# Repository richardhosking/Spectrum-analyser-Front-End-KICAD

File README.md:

# Spectrum-analyser-Front-End-KICAD

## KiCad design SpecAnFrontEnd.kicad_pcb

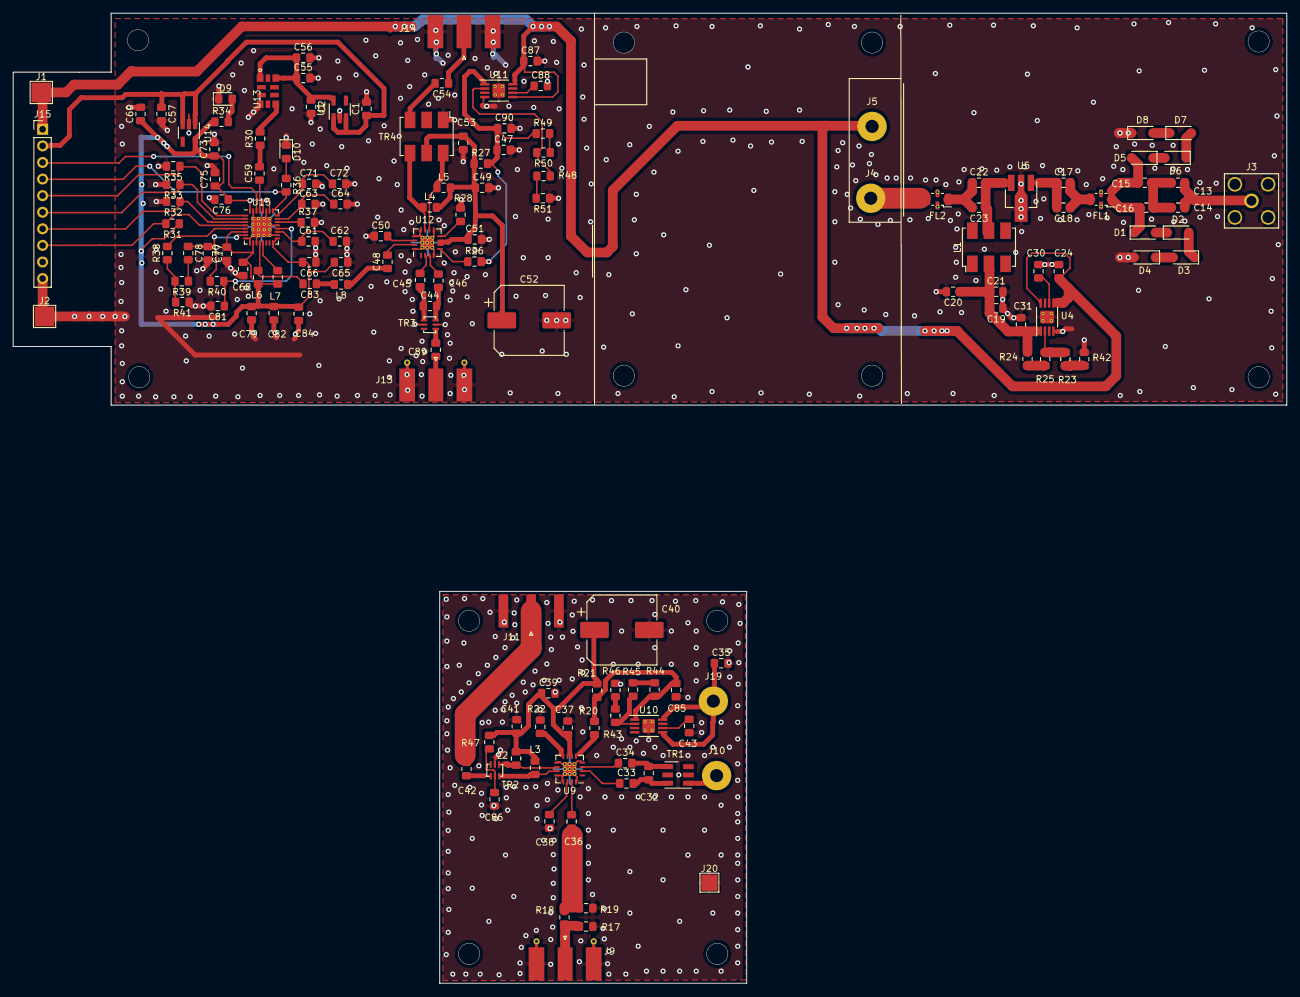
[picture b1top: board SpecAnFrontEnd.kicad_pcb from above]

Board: 2 copper layers, 195.0 x 148.5 mm, 151 parts (0 on the bottom side), 90 nets.

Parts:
C1, C2, C19, C39, C51, C57, C60: 1u; C_0805_2012Metric_Pad1.15x1.40mm_HandSolder
C13, C16, C18, C23, C33, C34, C36, C38, C55, C62, C64, C65, C72, C73, C75, C84: 100n; C_0805_2012Metric_Pad1.15x1.40mm_HandSolder
C14, C15, C17, C21, C22, C45, C46, C48, C50, C56, C79, C82: 100p; C_0805_2012Metric_Pad1.15x1.40mm_HandSolder
C20, C30, C37, C41, C43, C47, C49, C53, C86, C88: 10n; C_0805_2012Metric_Pad1.15x1.40mm_HandSolder
C24, C31, C35, C85, C87, C90: 10u; C_0805_2012Metric_Pad1.15x1.40mm_HandSolder
C32, C44: 0.6p; C_0805_2012Metric_Pad1.15x1.40mm_HandSolder
C40, C52: 220u; CP_Elec_10x10.5
C42, C89: 4p7; C_0805_2012Metric_Pad1.15x1.40mm_HandSolder
C54, C59, C83: 1n; C_0805_2012Metric_Pad1.15x1.40mm_HandSolder
C61, C63, C66, C68, C70, C71, C76: 10p; C_0805_2012Metric_Pad1.15x1.40mm_HandSolder
C77: 2n7; C_0805_2012Metric_Pad1.15x1.40mm_HandSolder
C78: 47n; C_0805_2012Metric_Pad1.15x1.40mm_HandSolder
C81: 680p; C_0805_2012Metric_Pad1.15x1.40mm_HandSolder
D1, D2, D3, D4, D5, D6, D7, D8: MMSD301T1G; D_SOD-123
D9: Power; D_0805_2012Metric_Pad1.15x1.40mm_HandSolder
D10: LOCK; D_0805_2012Metric_Pad1.15x1.40mm_HandSolder
FL1, FL2: LFCN-2600; Filter_Mini-Circuits_FV1206
J1: +V; TestPoint_Pad_3.0x3.0mm
J2: TestPoint_Pad_3.0x3.0mm
J3: Input; SMA_Amphenol_132203-12_Horizontal
J4: OUT to First Mixer; SolderWirePad_1x01_Drill2mm
J5, J19: +V; SolderWirePad_1x01_Drill2mm
J9: LO IN; SMA_Molex_73251-1153_EdgeMount_Horizontal
J10: Conn_Coaxial; SolderWirePad_1x01_Drill2mm
J11: Conn_Coaxial; SMA_Amphenol_132289_EdgeMount
J13, J14: Conn_Coaxial; SMA_Molex_73251-1153_EdgeMount_Horizontal
J15: Data; PinHeader_1x10_P2.54mm_Vertical
J20: GND; TestPoint_Pad_2.5x2.5mm
L1: ADCH-80+; Mini-Circuits_CD542_H2.84mm
L2, L3: 2nH; L_0805_2012Metric_Pad1.15x1.40mm_HandSolder
L4, L5: 22n; L_0805_2012Metric_Pad1.15x1.40mm_HandSolder
L6, L7: 7n5; L_0805_2012Metric_Pad1.15x1.40mm_HandSolder
L8: 1n9; L_0805_2012Metric_Pad1.15x1.40mm_HandSolder
R17, R19, R38: DNI; R_0805_2012Metric_Pad1.15x1.40mm_HandSolder
R18, R30, R41, R47: 0R; R_0805_2012Metric_Pad1.15x1.40mm_HandSolder
R20, R26, R31, R32, R33, R35: 10K; R_0805_2012Metric_Pad1.15x1.40mm_HandSolder
R21, R27: 0.5R; R_0805_2012Metric_Pad1.15x1.40mm_HandSolder
R22, R28: 4K75; R_0805_2012Metric_Pad1.15x1.40mm_HandSolder
R23, R43, R48: 22K; R_0805_2012Metric_Pad1.15x1.40mm_HandSolder
R24, R44, R49: 68K; R_0805_2012Metric_Pad1.15x1.40mm_HandSolder
R25, R45, R50: 8K2; R_0805_2012Metric_Pad1.15x1.40mm_HandSolder
R34, R36: 100R; R_0805_2012Metric_Pad1.15x1.40mm_HandSolder
R37: 4K7; R_0805_2012Metric_Pad1.15x1.40mm_HandSolder
R39: 360R; R_0805_2012Metric_Pad1.15x1.40mm_HandSolder
R40: 1K; R_0805_2012Metric_Pad1.15x1.40mm_HandSolder
R42, R46, R51: 1K8; R_0805_2012Metric_Pad1.15x1.40mm_HandSolder
TR1: TCM1-63AX; Mini-Circuits_DB1627
TR2, TR3: NCS1-422; Minicircuits_GE0805C-1
TR4: ADT4-5WT; Mini-Circuits_CD637_H5.23mm
U1, U14: ADP150; SOT-23-5_HandSoldering
U4, U10, U11: TPSA49; MSOP-8-1EP_3x3mm_P0.65mm_EP1.95x2.15mm_ThermalVias
U5: MMG38151; SOT-89-3_Handsoldering
U9, U12: LTC5510; QFN-16-1EP_4x4mm_P0.65mm_EP2.1x2.1mm_ThermalVias
U13: SiT5156
U15: ADF4351; LFCSP-32-1EP_5x5mm_P0.5mm_EP3.1x3.1mm_ThermalVias

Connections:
+V: C1.1, C24.1, C35.1, C57.1, C87.1, J1.1, J5.1, J15.1, J19.1, U1.1, U1.3, U4.5, U4.8, U10.5, U10.8, U11.5, U11.8, U14.1, U14.3
/First Mixer/U9VCC: C37.1, C39.1, C40.1, C41.1, L2.2, L3.1, R21.1, R47.1, U9.6, U9.7
/Second LO/AVDD2LO: C60.1, C65.2, C66.2, C68.2, C70.2, C73.1, C75.1, C76.1, C79.1, C82.1, C84.1, L6.2, L7.1, R31.1, R34.1, U14.5, U15.6, U15.10, U15.16, U15.17, U15.26, U15.28, U15.32
/Second LO/AVDDOSC: C2.1, C55.1, C56.1, U1.5, U13.1, U13.9
GND: C1.2, C2.2, C19.1, C20.2, C21.2, C24.2, C30.2, C31.2, C35.2, C37.2, C38.1, C39.2, C40.2, C41.2, C43.2, C47.2, C49.2, C50.1, C51.2, C52.2, C53.2, C55.2, C56.2, C57.2, C60.2, C61.2, C62.2, C63.2, C64.2, C65.1, C66.1, C68.1, C70.1, C71.2, C72.2, C73.2, C75.2, C76.2, C77.2, C81.2, C85.2, C86.2, C87.2, C88.2, C90.2, D4.2, D8.1, D9.1, D10.1, FL1.2, FL1.4, FL2.2, FL2.4, J2.1, J3.2, J9.2, J11.2, J13.2, J14.2, J15.10, J20.1, R17.2, R19.2, R22.2, R28.2, R32.2, R33.2, R35.2, R37.2, R41.1, R42.1, R46.1, R51.1, TR1.2, TR2.5, TR3.2, TR3.5, TR4.1, U1.2, U4.9, U5.2, U9.4, U9.9, U9.12, U9.13, U9.16, U9.17, U10.9, U11.9, U12.4, U12.9, U12.12, U12.13, U12.16, U12.17, U13.4, U14.2, U15.8, U15.9, U15.11, U15.18, U15.21, U15.27, U15.31, U15.33
LO: C48.1, L8.1
unnamed: C13.1, C14.2, J3.1
unnamed: C13.2, C14.1, C15.2, C16.1
unnamed: C15.1, C16.2, D1.1, D5.2, FL1.1
unnamed: C17.1, C18.2, U5.1
unnamed: C17.2, C18.1, FL1.3
unnamed: C19.2, C20.1, C21.1, C31.1, L1.3, R24.1, U4.1
unnamed: C22.1, C23.2, FL2.1
unnamed: C22.2, C23.1, L1.6, U5.3
unnamed: C30.1, U4.6
unnamed: C32.1, C33.2, TR1.4
unnamed: C32.2, C34.2, TR1.6
unnamed: C33.1, U9.2
unnamed: C34.1, U9.3
unnamed: C36.1, R18.1, R19.1
unnamed: C36.2, U9.15
unnamed: C38.2, U9.14
unnamed: C42.1, J11.1
unnamed: C42.2, TR2.1
unnamed: C43.1, U10.6
unnamed: C44.1, C45.2, TR3.4
unnamed: C44.2, C46.2, TR3.3
unnamed: C45.1, U12.2
unnamed: C46.1, U12.3
unnamed: C47.1, C90.1, R26.2, R27.2, R49.1, U11.1
unnamed: C48.2, U12.15
unnamed: C49.1, C51.1, C52.1, C53.1, L4.2, L5.2, R27.1, TR4.5, U12.6, U12.7
unnamed: C50.2, U12.14
unnamed: C54.1, J14.1
unnamed: C54.2, TR4.3
unnamed: C59.1, U15.29
unnamed: C59.2, R30.1
unnamed: C61.1, C62.1, U15.19
unnamed: C63.1, C64.1, U15.23
unnamed: C71.1, C72.1, U15.24
unnamed: C77.1, C78.1, R40.2, U15.7
unnamed: C78.2, R39.1
unnamed: C79.2, C82.2, C84.2
unnamed: C81.1, R40.1, U15.20
unnamed: C83.1, L8.2
unnamed: C83.2, L6.1, U15.12
unnamed: C85.1, R20.2, R21.2, R44.1, U10.1
unnamed: C86.1, R47.2, TR2.2
unnamed: C88.1, U11.6
unnamed: C89.1, TR3.1
unnamed: C89.2, J13.1
unnamed: D1.2, D2.1
unnamed: D2.2, D3.1
unnamed: D3.2, D4.1
unnamed: D5.1, D6.2
unnamed: D6.1, D7.2
unnamed: D7.1, D8.2
unnamed: D9.2, R34.2
unnamed: D10.2, R36.1
unnamed: FL2.3, J4.1
unnamed: J9.1, R17.1, R18.2
unnamed: J10.1, TR1.3
unnamed: J15.3, U15.30
unnamed: J15.4, R36.2, U15.25
unnamed: J15.5, R35.1, U15.1
unnamed: J15.6, R33.1, U15.2
unnamed: J15.7, R32.1, U15.3
unnamed: J15.8, R31.2, U15.4
unnamed: L2.1, TR2.3, U9.11
unnamed: L3.2, TR2.4, U9.10
unnamed: L4.1, TR4.4, U12.11
unnamed: L5.1, TR4.6, U12.10
unnamed: L7.2, U15.13
unnamed: R20.1, U9.5
unnamed: R22.1, U9.8
unnamed: R23.1, R42.2
unnamed: R23.2, R25.2, U4.2
unnamed: R24.2, R25.1
unnamed: R26.1, U12.5
unnamed: R28.1, U12.8
unnamed: R30.2, U13.6
unnamed: R37.1, U15.22
unnamed: R38.1, R39.2, R41.2
unnamed: R38.2, U15.5
unnamed: R43.1, R46.2
unnamed: R43.2, R45.2, U10.2
unnamed: R44.2, R45.1
unnamed: R48.1, R51.2
unnamed: R48.2, R50.2, U11.2
unnamed: R49.2, R50.1

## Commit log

2020-10-31 Front End Nov 2020
